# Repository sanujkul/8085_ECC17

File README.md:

# 8085_ECC17
### This is project done under guidance of Prof D.V. Gadre in his lab The Centre for Electronics Design and Technology

### The aim was to make a project using 8085 microprocessor. We made a project to display location using GPS NEO 6M and required fields were displayed on the LCD.

### In this readme we will display the Project Report, so it will be lot different from actual README.md

The video demonstrating the of the project can be found at 
https://youtu.be/zBtNmY20Y-0

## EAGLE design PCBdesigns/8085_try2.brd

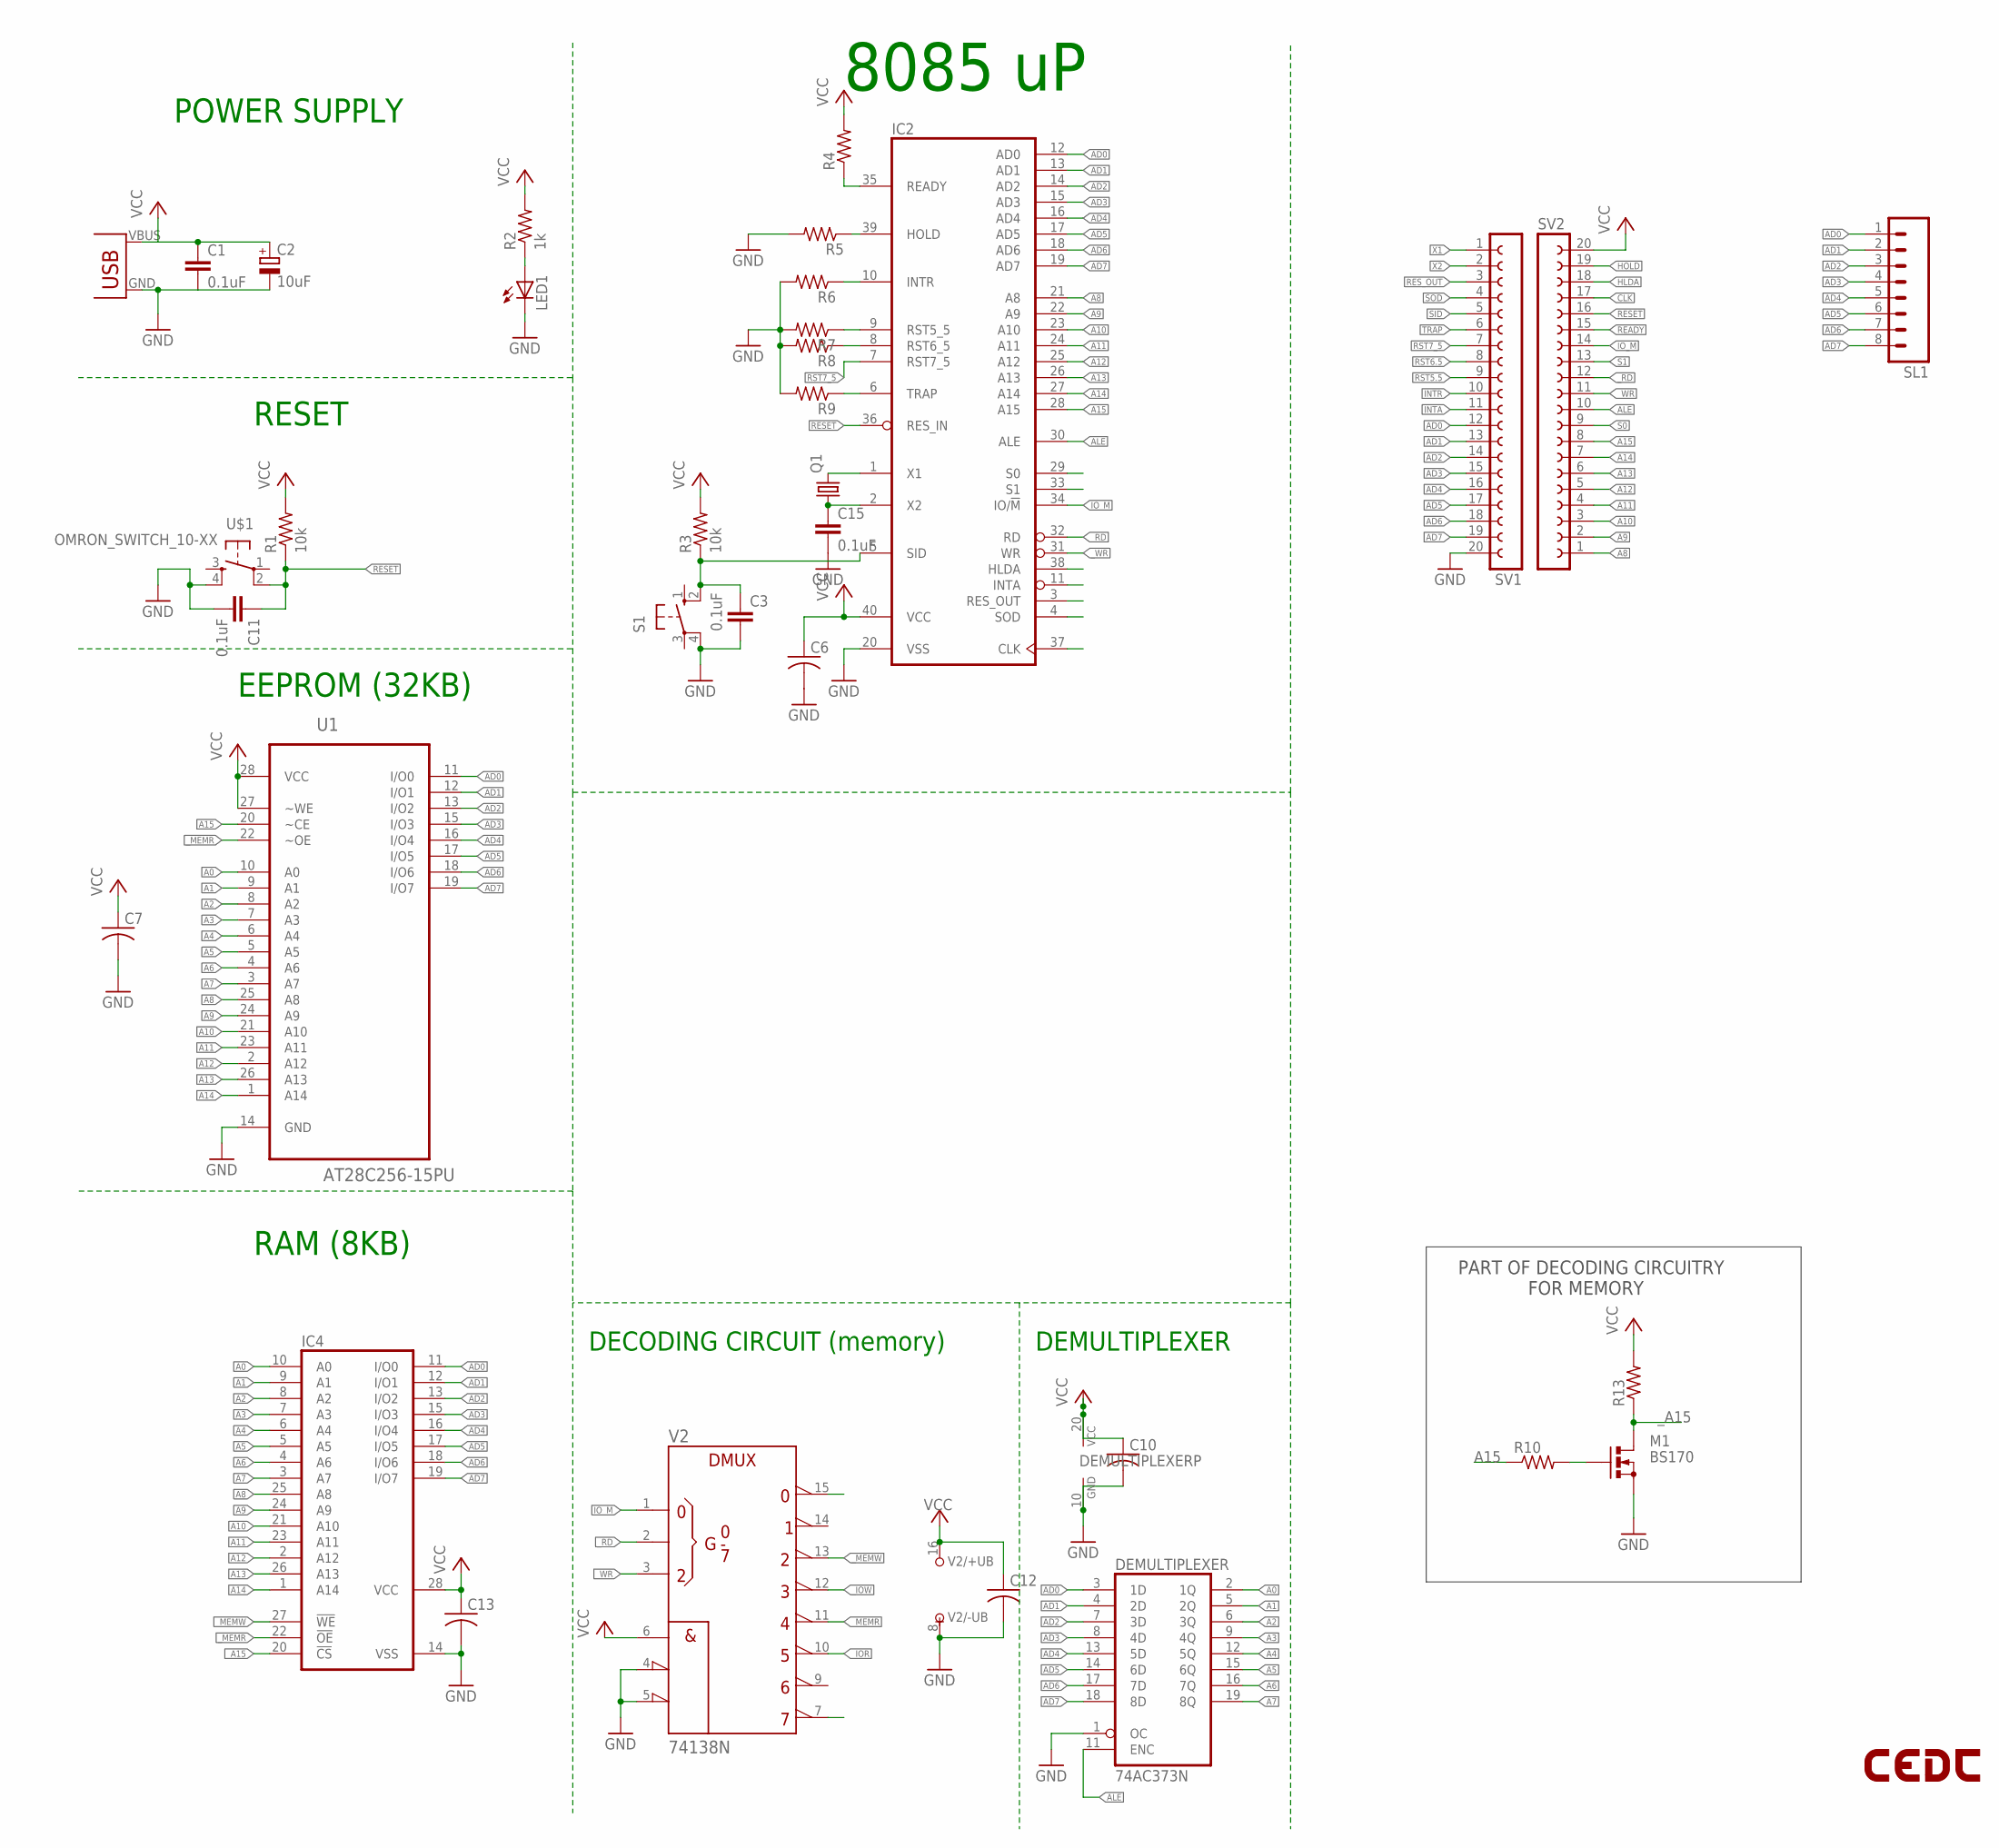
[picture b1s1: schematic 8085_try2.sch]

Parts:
C1, C3, C11, C15: 0.1uF; C2.5-3
C2: 10uF; E2,5-6
C6, C7, C10, C12, C13: CAP0805; C0805
DEMULTIPLEXER: 74AC373N; DIL20
IC2: 8085; DIL40
IC4: 62256P; DIL28-6
LED1: LED3MM
LOGO1: LOGO-CEDTBOT-18MM; LOGO-CEDT-BOT-18MM
M1: BS170; SOT54E
Q1: CRYSTALHC49US; HC49US
R1, R3: 10k; 0207/7
R2: 1k; 0207/7
R4, R5, R6, R7, R8, R9: RESISTOR0805; R0805
R10, R13: R-US_0204/5; 0204/5
S1: 40-XX; B3F-40XX
SL1: M08; 08P
SV1, SV2: FE20-1; FE20
U1: AT28C256-15PU; DIP254P1524X482-28
U$1: OMRON_SWITCH_10-XX; B3F-10XX
U$2: USB(POWER)
V2: 74138N; DIL16

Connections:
A0: DEMULTIPLEXER.2 (1Q), IC4.10 (A0), U1.10 (A0)
A1: DEMULTIPLEXER.5 (2Q), IC4.9 (A1), U1.9 (A1)
A2: DEMULTIPLEXER.6 (3Q), IC4.8 (A2), U1.8 (A2)
A3: DEMULTIPLEXER.9 (4Q), IC4.7 (A3), U1.7 (A3)
A4: DEMULTIPLEXER.12 (5Q), IC4.6 (A4), U1.6 (A4)
A5: DEMULTIPLEXER.15 (6Q), IC4.5 (A5), U1.5 (A5)
A6: DEMULTIPLEXER.16 (7Q), IC4.4 (A6), U1.4 (A6)
A7: DEMULTIPLEXER.19 (8Q), IC4.3 (A7), U1.3 (A7)
A8: IC2.21 (A8), IC4.25 (A8), SV2.1, U1.25 (A8)
A9: IC2.22 (A9), IC4.24 (A9), SV2.2, U1.24 (A9)
A10: IC2.23 (A10), IC4.21 (A10), SV2.3, U1.21 (A10)
A11: IC2.24 (A11), IC4.23 (A11), SV2.4, U1.23 (A11)
A12: IC2.25 (A12), IC4.2 (A12), SV2.5, U1.2 (A12)
A13: IC2.26 (A13), IC4.26 (A13), SV2.6, U1.26 (A13)
A14: IC2.27 (A14), IC4.1 (A14), SV2.7, U1.1 (A14)
A15: IC2.28 (A15), R10.1, SV2.8, U1.20 (~CE)
AD0: DEMULTIPLEXER.3 (1D), IC2.12 (AD0), IC4.11 (I/O0), SL1.1, SV1.12, U1.11 (I/O0)
AD1: DEMULTIPLEXER.4 (2D), IC2.13 (AD1), IC4.12 (I/O1), SL1.2, SV1.13, U1.12 (I/O1)
AD2: DEMULTIPLEXER.7 (3D), IC2.14 (AD2), IC4.13 (I/O2), SL1.3, SV1.14, U1.13 (I/O2)
AD3: DEMULTIPLEXER.8 (4D), IC2.15 (AD3), IC4.15 (I/O3), SL1.4, SV1.15, U1.15 (I/O3)
AD4: DEMULTIPLEXER.13 (5D), IC2.16 (AD4), IC4.16 (I/O4), SL1.5, SV1.16, U1.16 (I/O4)
AD5: DEMULTIPLEXER.14 (6D), IC2.17 (AD5), IC4.17 (I/O5), SL1.6, SV1.17, U1.17 (I/O5)
AD6: DEMULTIPLEXER.17 (7D), IC2.18 (AD6), IC4.18 (I/O6), SL1.7, SV1.18, U1.18 (I/O6)
AD7: DEMULTIPLEXER.18 (8D), IC2.19 (AD7), IC4.19 (I/O7), SL1.8, SV1.19, U1.19 (I/O7)
ALE: DEMULTIPLEXER.11 (ENC), IC2.30 (ALE), SV2.10
CLK: IC2.37 (CLK), SV2.17
GND: C1.2, C2.-, C3.2, C6.2, C7.2, C10.2, C11.2, C12.2, C13.2, C15.2, DEMULTIPLEXER.1 (OC), DEMULTIPLEXER.10 (GND), IC2.20 (VSS), IC4.14 (VSS), LED1.K (C), M1.S, R5.2, R6.2, R7.2, R8.2, R9.2, S1.4 (P1), SV1.20, U1.14 (GND), U$1.4 (S1), U$2.GND, V2.4 (!G2A), V2.5 (!G2B), V2.8 (-UB)
HLDA: IC2.38 (HLDA), SV2.18
HOLD: IC2.39 (HOLD), R5.1, SV2.19
INTA: IC2.11 (INTA), SV1.11
INTR: IC2.10 (INTR), R6.1, SV1.10
IO_M: IC2.34 (IO/!M), SV2.14, V2.1 (A)
unnamed: M1.G, R10.2
unnamed: LED1.A, R2.1
READY: IC2.35 (READY), R4.1, SV2.15
RESET: C11.1, IC2.36 (RES_IN), R1.1, SV2.16, U$1.2 (P1)
RES_OUT: IC2.3 (RES_OUT), SV1.3
RST5.5: IC2.9 (RST5_5), R7.1, SV1.9
RST6.5: IC2.8 (RST6_5), R8.1, SV1.8
RST7_5: IC2.7 (RST7_5), SV1.7
S0: IC2.29 (S0), SV2.9
S1: IC2.33 (S1), SV2.13
SID: C3.1, IC2.5 (SID), R3.1, S1.2 (S1), SV1.5
SOD: IC2.4 (SOD), SV1.4
TRAP: IC2.6 (TRAP), R9.1, SV1.6
VCC: C1.1, C2.+, C6.1, C7.1, C10.1, C12.1, C13.1, DEMULTIPLEXER.20 (VCC), IC2.40 (VCC), IC4.28 (VCC), R1.2, R2.2, R3.2, R4.2, R13.2, SV2.20, U1.27 (~WE), U1.28 (VCC), U$2.VBUS (VCC), V2.6 (G1), V2.16 (+UB)
X1: IC2.1 (X1), Q1.2, SV1.1
X2: C15.1, IC2.2 (X2), Q1.1, SV1.2
_A15: IC4.20 (!CS), M1.D, R13.1
_IOR: V2.10 (Y5)
_IOW: V2.12 (Y3)
_MEMR: IC4.22 (!OE), U1.22 (~OE), V2.11 (Y4)
_MEMW: IC4.27 (!WE), V2.13 (Y2)
_RD: IC2.32 (RD), SV2.12, V2.2 (B)
_WR: IC2.31 (WR), SV2.11, V2.3 (C)

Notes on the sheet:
8085 uP
POWER SUPPLY
RESET
EEPROM (32KB)
DECODING CIRCUIT (memory)
RAM (8KB)
DEMULTIPLEXER
PART OF DECODING CIRCUITRY FOR MEMORY

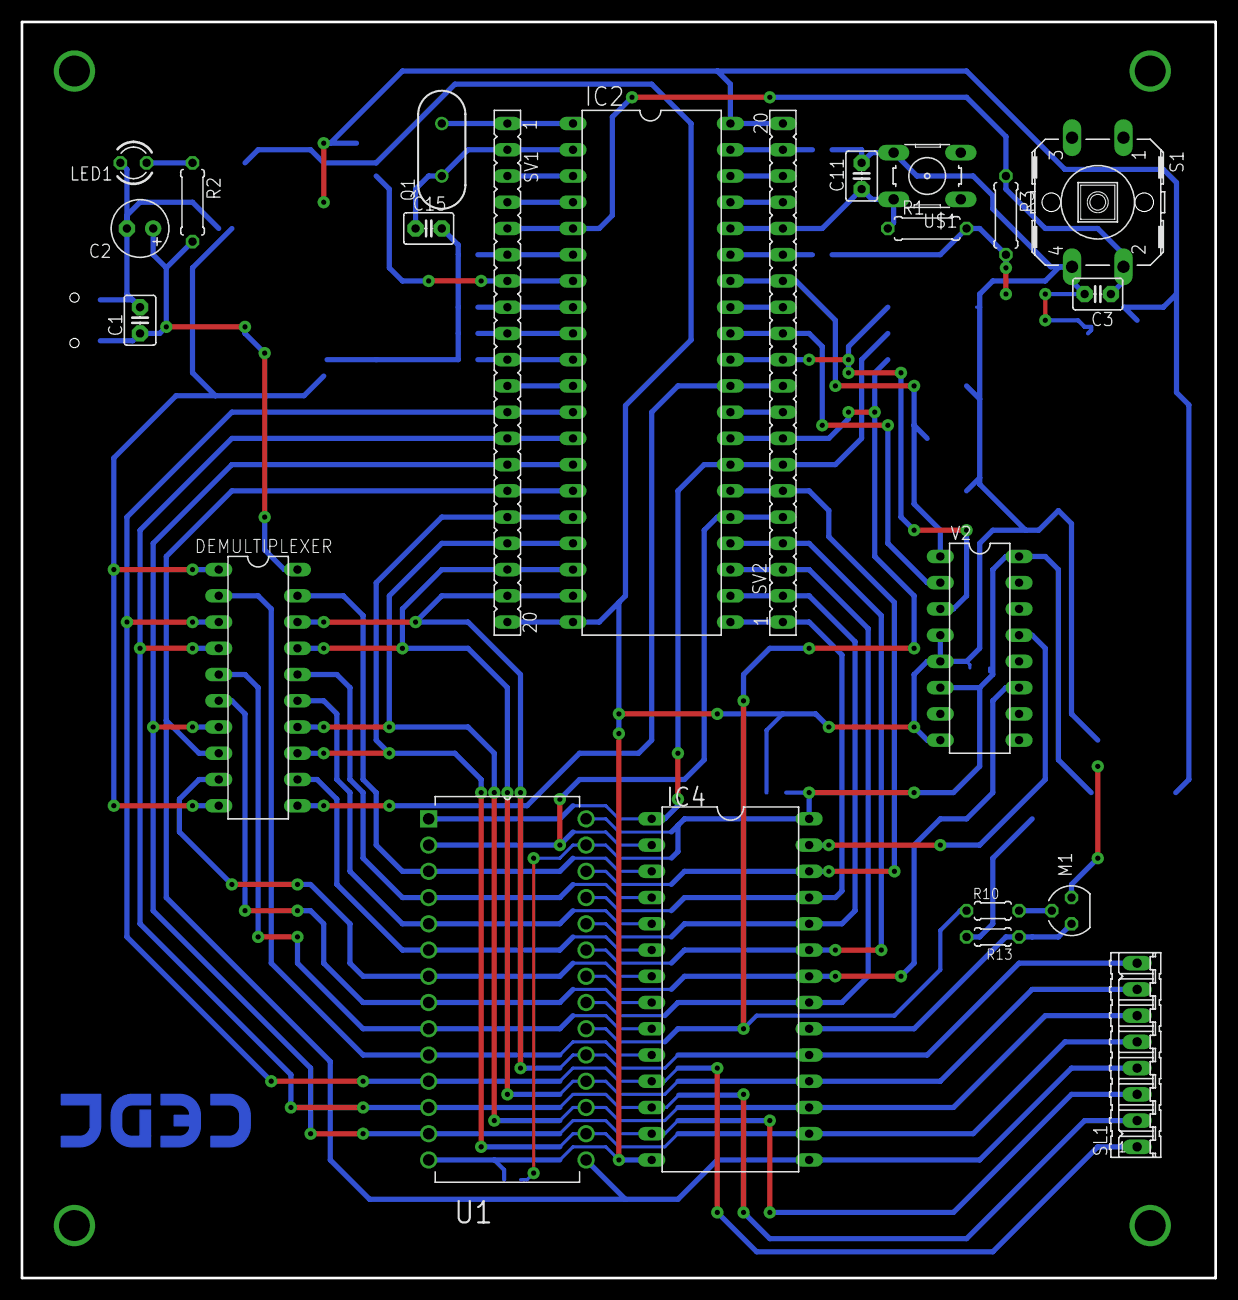
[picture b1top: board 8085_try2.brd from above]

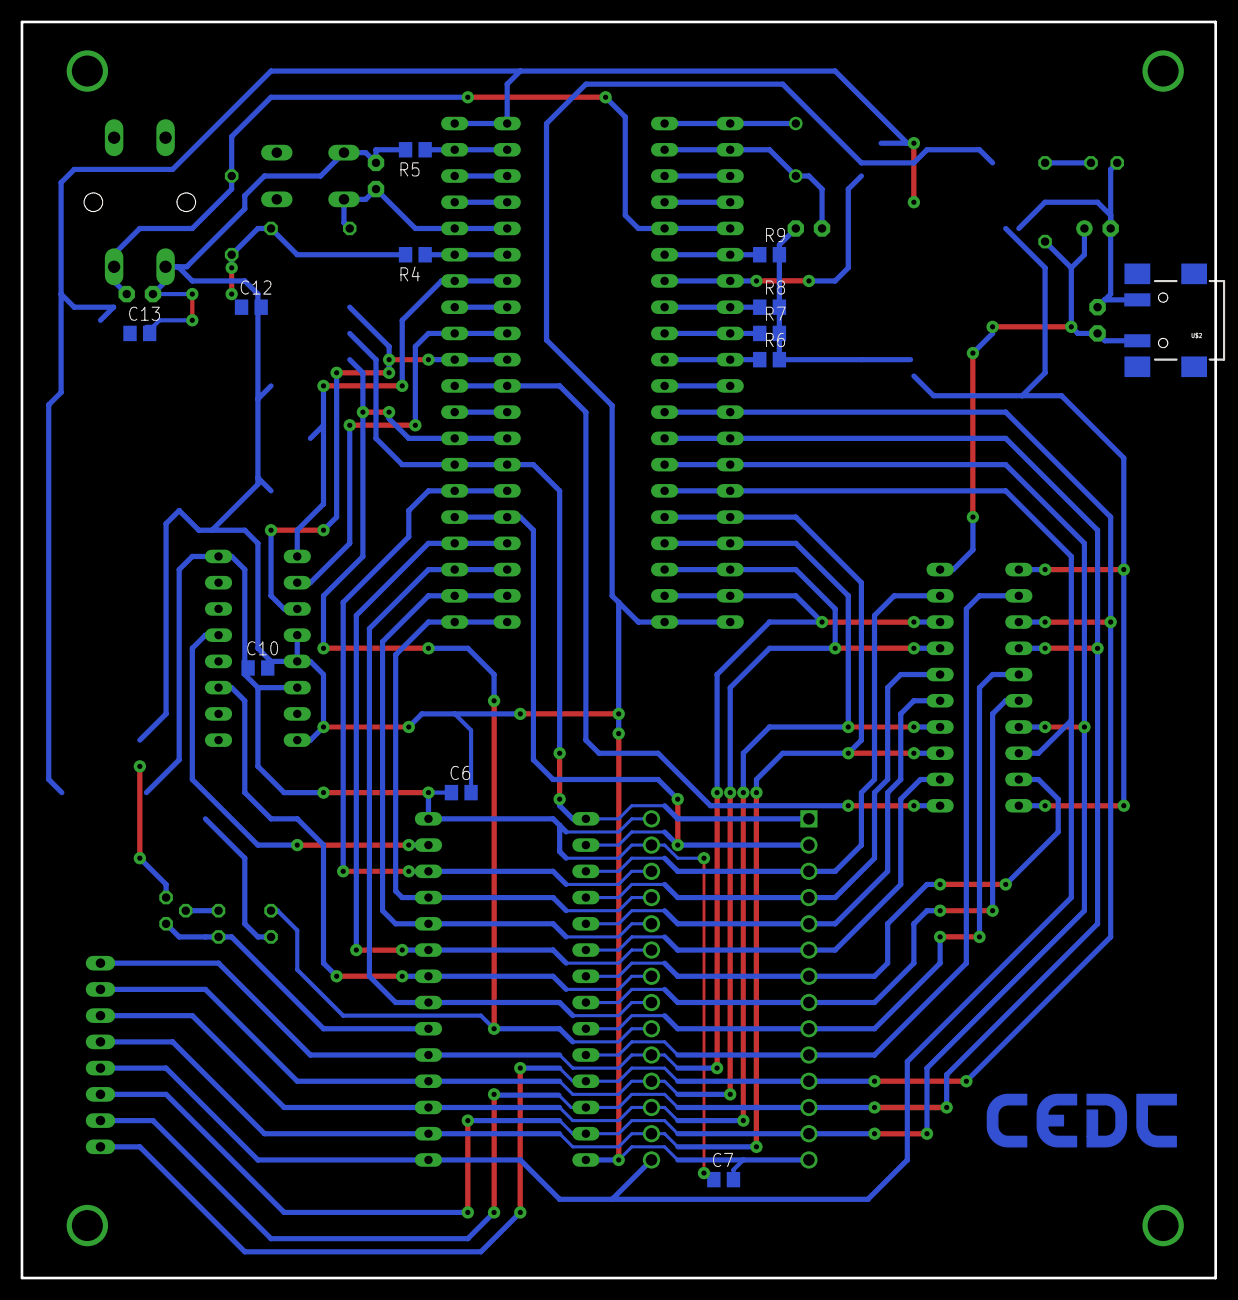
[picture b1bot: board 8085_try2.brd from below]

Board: 2 copper layers, 115.5 x 121.6 mm, 36 parts (12 on the bottom side), 53 nets.

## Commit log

2019-11-11 Removed extra part form Apoorv's
2019-11-12 Trying to run board2 with nano
2019-12-15 More tests
2020-03-12 Adding all the hex and asm files
2020-06-21 The project Documentation
2020-06-29 Organised the files
2020-06-29 Adding 10 images
2020-06-29 Adding 8 more images
2020-06-29 Adding beggining
2020-06-29 Adding and correcting
